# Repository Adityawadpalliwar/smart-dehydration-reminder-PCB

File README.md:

# Smart Hydration Reminder PCB

A compact, low-power, wireless-capable PCB designed to live in a water bottle base or sleeve. It detects when you drink using a 6-axis IMU, keeps a running record of intake events, and reminds you with a buzzer when you have gone too long without drinking. A companion phone app can connect over Bluetooth LE to adjust reminder intervals, mute alerts, read battery status and push firmware updates.

| | |
|---|---|
| **MCU** | Espressif ESP32-C3-MINI-1U-H4 (RISC-V, Wi-Fi + Bluetooth 5 LE) |
| **Motion sensing** | Bosch BMI270 6-axis IMU with wake-on-motion |
| **Power** | USB-C charging, 1S Li-ion/LiPo cell, 3.3 V LDO with hard-off slide switch |
| **Feedback** | Active buzzer, red/green battery LEDs, charge-status LED |
| **Input** | Tactile snooze/log button, slide power switch |
| **Board** | 4-layer PCB, 37.48 mm × 29.99 mm |

---

## Table of Contents

1. [Design Overview](#1-design-overview)
2. [System Architecture](#2-system-architecture)
3. [Power Subsystem](#3-power-subsystem)
4. [Compute and Connectivity](#4-compute-and-connectivity)
5. [Motion Sensing and Drinking Detection](#5-motion-sensing-and-drinking-detection)
6. [User Interface and Feedback](#6-user-interface-and-feedback)
7. [PCB Design](#7-pcb-design)
8. [Pin Assignment](#8-pin-assignment)
9. [Bill of Materials (Key Components)](#9-bill-of-materials-key-components)
10. [Power Considerations](#10-power-considerations)
11. [Known Limitations and Planned Improvements](#11-known-limitations-and-planned-improvements)
12. [Conclusion](#12-conclusion)

---

## 1. Design Overview

The platform combines motion intelligence, multi-modal alerts, low-power telemetry and dual-mode connectivity (Wi-Fi / Bluetooth LE) to monitor drinking patterns, track the interval between sips and deliver adaptive reminders.

The hardware is organised as four layers, each building on the one before:

| Layer | Function | Key parts |
|---|---|---|
| **Charging** | Safe single-cell Li-ion charging from USB-C | J1, USBLC6-2SC6, MCP73831 |
| **Power gating** | User-operated hard-off that shuts down the entire downstream system | S1, RT9080 LDO |
| **Compute and sense** | Application logic, radio, motion detection, battery monitoring | ESP32-C3-MINI-1U, BMI270 |
| **Feedback** | Audible reminders and visual status | Buzzer, LEDs, tactile button |

A central design decision is that the slide switch gates the **LDO itself**, not just the buzzer. Flipping it to OFF removes power from every downstream block (MCU, IMU, LEDs, buzzer driver), giving true zero downstream draw for storage or travel, while the charger and cell remain upstream so the battery still charges over USB regardless of switch position.

---

## 2. System Architecture

```mermaid
flowchart LR
    USB["USB-C receptacle (J1)"] --> ESD["ESD protection (U6)"]
    ESD -- "D+ / D-" --> MCU
    USB -- "VBUS" --> CHG["MCP73831 charger (U4)"]
    CHG --> BAT[("1S Li-ion / LiPo cell")]
    BAT --> LDO["RT9080 3.3 V LDO (IC1)"]
    SW["Slide switch (S1)"] -- "EN control" --> LDO
    LDO --> RAIL["3.3 V rail"]
    RAIL --> MCU["ESP32-C3-MINI-1U (U2)"]
    RAIL --> IMU["BMI270 IMU (U3)"]
    IMU -- "I2C + INT1" --> MCU
    BAT -- "Divider R14/R15" --> MCU
    MCU --> LEDS["Battery LEDs (D2, D3)"]
    MCU --> BUZ["Buzzer driver (Q1, U5)"]
    BTN["Push button (S2)"] --> MCU
```

Power flows from USB-C through the charger into the cell, then through the LDO to the 3.3 V rail. Data flows between the IMU, buttons and MCU, and the MCU drives the LEDs and buzzer.

---

## 3. Power Subsystem

### 3.1 USB-C Input and ESD Protection

- **Connector:** USB Type-C 16-pin receptacle (J1), used for USB 2.0 data (D+/D−) and VBUS/GND.
- **CC termination:** 5.1 kΩ pull-down resistors (R1, R2) on CC1 and CC2 identify the board as a sink, so a Type-C source enables VBUS at 5 V.
- **Transient protection:** A TVS diode array (U6, USBLC6-2SC6) sits directly beside the receptacle and clamps ESD on the data lines, rated to ±15 kV air discharge (IEC 61000-4-2).

### 3.2 Battery Charging

- **Charge controller:** Microchip MCP73831T-2ACI/OT (U4), SOT-23-5, constant-current / constant-voltage charging to 4.2 V.
- **Charge current:** Set by R5 on the PROG pin:

  ```
  I_CHG = 1000 V / R_PROG
  ```

  With R5 = 2 kΩ the fast-charge current is **500 mA**.
- **Status indication:** The open-drain STAT pin drives the charge LED (D1) through R4 = 4.7 kΩ. D1 is lit during the CC/CV phase and goes off (high-impedance) once charge terminates.
- **Cell:** 1S Li-ion/LiPo connected at pads J2/J3 (4.2 V max). A cell with a built-in protection circuit is required, as the board does not include its own over-discharge protection.

### 3.3 Hard-Off Power Switch

- **Switch:** C&K JS202011SCQN (S1), a subminiature surface-mount SPDT slide switch.
- **Rationale:** Rather than routing the ESP32-C3's high RF supply current (transmit spikes around 350 mA) through small mechanical switch contacts, which causes contact wear and voltage droop, the switch drives the high-impedance **EN** input of the LDO.
- **Wiring:**

  | S1 pin | Connection |
  |---|---|
  | Pin 1 (outer) | VBAT |
  | Pin 2 (common) | EN pin of IC1 |
  | Pin 3 (outer) | GND |

  R13 = 100 kΩ additionally ties EN to GND.
- **OFF state:** EN is driven to GND, the LDO enters shutdown (typically below 0.1 µA), and nothing downstream draws current.
- **Charging is independent of the switch.** The charger and cell sit upstream of the switch, so a switched-off device still charges.
- **Trade-off:** When switched off, the MCU cannot log the event, cannot save state beyond what is already in flash, and cannot be reached over BLE. This is intentional for a hard off.
- **Control roles:** The tactile button (S2) is the fast, momentary snooze/silence control. The slide switch is purely the full power gate.

### 3.4 3.3 V Regulation

- **Regulator:** Richtek RT9080-33GJ5 (IC1), TSOT-23-5.
- **Quiescent current:** about 2 µA typical, versus roughly 5 mA for a classic AMS1117-class regulator, which would drain a small cell in days.
- **Output capability:** 600 mA continuous, above the ESP32-C3 peak transient demand (about 500 mA system requirement).
- **Dropout:** 310 mV at 600 mA. Dropout scales with load, so at the light average loads of this application the regulator holds 3.3 V until the cell is nearly empty (about 3.0 V). Under a full 600 mA load, regulation needs roughly 3.6 V at the input. Use the ESP32-C3 brown-out detector for the low-voltage end.

---

## 4. Compute and Connectivity

### 4.1 MCU

- **Module:** Espressif ESP32-C3-MINI-1U-H4 (U2)
- **Core:** 32-bit single-core RISC-V, up to 160 MHz, 4 MB embedded flash
- **RF:** U.FL connector for an external antenna, which avoids the detuning that liquid volumes inside a water bottle would cause on an on-board antenna

The MCU runs the whole system: timers, the buzzer state machine, IMU handling, ADC readings, intake logging and the BLE/Wi-Fi link. Choosing a radio-capable MCU means app connectivity costs no additional hardware.

### 4.2 Mobile Ecosystem and Firmware Interoperability

- **BLE control:** A Bluetooth 5 LE GATT server lets the companion app modify reminder intervals, mute acoustic alerts, read real-time battery status and push over-the-air (OTA) firmware updates.
- **Intake logging:** Drinking events are stored locally in non-volatile storage (NVS flash) and batch-synchronised to the cloud when Wi-Fi is reachable.
- **Radio versus battery life:** BLE activity draws tens of milliamps while active, against microamps in deep sleep. The connection and advertising schedule directly trades app responsiveness (for example, muting a reminder remotely) against battery life, and is a key firmware tuning parameter.

---

## 5. Motion Sensing and Drinking Detection

### 5.1 Sensor

- **IC:** Bosch BMI270 (U3), a 16-bit ultra-low-power 6-axis IMU (3-axis accelerometer + 3-axis gyroscope).
- **Power:** below 685 µA in full-performance mode, and a few microamps in suspend.
- **Interface:** I²C on IO2 (SDA) and IO3 (SCL) with 4.7 kΩ pull-ups (R7, R8). Decoupling on C6/C7. Ensure CSB is strapped high for I²C mode and SDO is strapped to set the address.

### 5.2 Drinking Detection Algorithm

Motion processing runs directly in firmware:

1. **Pickup detection.** High-pass-filtered Z-axis acceleration thresholds detect the bottle being lifted from a resting surface.
2. **Tilt estimation.** Pitch and roll dynamics give the tilt angle relative to gravity:

   ```
   θ_tilt = atan2( A_y , sqrt(A_x² + A_z²) )
   ```
3. **Sip validation.** A sip event is confirmed when the tilt exceeds **45°** for at least **1.5 s**, followed by a controlled lowering movement.
4. **Timer reset.** Each verified sip resets the reminder countdown, so users who hydrate naturally are never nagged.

### 5.3 Deep Sleep with Wake-on-Motion

- BMI270 **INT1** (pin 4) connects to the RTC-capable pin **IO4** of the ESP32-C3.
- When idle, the ESP32-C3 sits in deep sleep (about 5 µA) while the BMI270 stays in its low-power motion-detect mode.
- Moving the bottle makes the BMI270 pulse INT1, waking the MCU to update intake telemetry and timer logs.

---

## 6. User Interface and Feedback

### 6.1 Battery Voltage Monitoring

- **Divider:** R14 = R15 = 100 kΩ halve the battery voltage:

  ```
  V_ADC = V_BAT × R15 / (R14 + R15) = V_BAT / 2
  ```
- **Range:** At V_BAT = 4.2 V, V_ADC = 2.1 V, inside the ESP32-C3 ADC range at 11 dB attenuation (0 to about 2.5 V). The divider feeds ADC pin **IO0**.
- **Noise filter:** C10 = 0.1 µF across R15 forms a low-pass filter with the 50 kΩ Thévenin resistance:

  ```
  f_c = 1 / (2π × 50 kΩ × 0.1 µF) ≈ 31.8 Hz
  ```

  This suppresses ripple from Wi-Fi/Bluetooth transmit bursts.
- **Firmware note:** The ESP32-C3 ADC is non-linear at the ends of its range, so use the calibrated ADC API (eFuse calibration values) rather than a simple linear conversion.

### 6.2 Visual Battery Telemetry

| LED | Colour | Pin | Resistor | Lit when |
|---|---|---|---|---|
| D3 | Green | IO5 | 470 Ω (R11) | V_BAT ≥ 3.5 V |
| D2 | Red | IO6 | 470 Ω (R12) | V_BAT < 3.5 V |
| D1 | Charge status | MCP73831 STAT | 4.7 kΩ (R4) | While charging |

Firmware drives IO5 high and IO6 low above the threshold, and the reverse below it.

### 6.3 Acoustic Alert Subsystem

- **Transducer:** TMB12A03 (U5), 3 V active electromagnetic buzzer.
- **Driver:** Alpha & Omega AO3400 N-channel MOSFET (Q1, SOT-23-3, V_DS = 30 V, I_D = 5.8 A) low-side switches the buzzer.
- **Gate drive:** IO7 (BUZZ net). R6 = 10 kΩ pulls the gate to GND so the buzzer cannot turn on during MCU reset or boot.
- **Flyback protection:** A 1N4148 diode (CR1) across the buzzer terminals clamps inductive spikes at turn-off.
- **Patterns:** The MCU gates IO7 using LEDC PWM to create beep rhythms, such as a gentle single chime versus an escalating pattern after ignored reminders. The same driver circuit serves every pattern.

### 6.4 Snooze and Log Button

- **Switch:** C&K PTS526 (S2), low-profile tactile.
- **Circuit:** IO1 with a 10 kΩ pull-up (R10) to 3.3 V and a 0.1 µF debounce capacitor (C9) to GND.
- **Short press (< 1 s):** acknowledges and silences an active alarm, and resets the reminder timer.
- **Long press (> 3 s):** manual logging trigger, or initiates Bluetooth pairing.

---

## 7. PCB Design

The board is a **four-layer PCB measuring 37.48 mm × 29.99 mm**, laid out to be as compact as possible so it fits inside a bottle base or sleeve.

### 7.1 Layer Stack-Up

| Layer | Role |
|---|---|
| **L1 (Top)** | Power distribution and component placement |
| **L2** | Continuous ground plane |
| **L3** | Signal routing |
| **L4 (Bottom)** | Power/ground pours and remaining routing |

The dedicated ground plane on L2 gives every top-layer signal a solid return path and keeps the RF-adjacent ESP32-C3 section and the mixed analogue/digital sections (ADC divider, I²C sensor) well referenced. Keeping signals on L3 between planes reduces coupling and improves noise immunity, and the power/ground pours on L4 keep supply impedance low across the board.

### 7.2 Placement

- **USB-C (J1)** on the left board edge for easy cable access, with the ESD array and CC resistors immediately beside it.
- **ESP32-C3 module (U2)** at the top centre, close to the board edge to keep the radio section clear of other circuitry.
- **BMI270 (U3)** and its pull-ups and decoupling near the MCU, keeping the I²C and interrupt traces short.
- **Charger (U4), LDO (IC1) and passives** grouped in the lower centre, keeping the power path compact.
- **Slide switch (S1) and tactile button (S2)** on the right edge for user access.
- **Buzzer (U5) and driver (Q1)** at the top right.
- **Battery pads (J2/J3)** on the left side beside the charging circuitry.

---

## 8. Pin Assignment

| MCU pin | Signal | Direction | Notes |
|---|---|---|---|
| IO0 | Battery voltage sense | Input (ADC) | Via R14/R15 divider, filtered by C10 |
| IO1 | Snooze/log button (S2) | Input | 10 kΩ pull-up, 0.1 µF debounce |
| IO2 | I²C SDA | Bidirectional | 4.7 kΩ pull-up (R7) |
| IO3 | I²C SCL | Output | 4.7 kΩ pull-up (R8) |
| IO4 | BMI270 INT1 | Input (RTC) | Deep-sleep wake source |
| IO5 | Green LED (D3) | Output | 470 Ω series resistor |
| IO6 | Red LED (D2) | Output | 470 Ω series resistor |
| IO7 | Buzzer drive (BUZZ) | Output (PWM) | Gate of Q1, 10 kΩ pull-down |

---

## 9. Bill of Materials (Key Components)

| Ref | Part | Function |
|---|---|---|
| J1 | USB Type-C 16-pin receptacle | Power and data input |
| U6 | USBLC6-2SC6 | ESD/TVS protection on USB data lines |
| U4 | MCP73831T-2ACI/OT | Single-cell Li-ion charger |
| IC1 | RT9080-33GJ5 | 3.3 V ultra-low-Iq LDO |
| S1 | C&K JS202011SCQN | Slide switch, hard-off (LDO enable) |
| U2 | ESP32-C3-MINI-1U-H4 | MCU with Wi-Fi/BLE, U.FL antenna |
| U3 | Bosch BMI270 | 6-axis IMU |
| Q1 | AO3400 | Logic-level N-MOSFET, buzzer low-side switch |
| U5 | TMB12A03 | 3 V active electromagnetic buzzer |
| CR1 | 1N4148 | Buzzer flyback diode |
| S2 | C&K PTS526 | Tactile snooze/log button |
| D1 / D2 / D3 | LEDs | Charge status / low battery (red) / battery OK (green) |
| J2 / J3 | Battery pads | 1S Li-ion/LiPo connection |
| R1, R2 | 5.1 kΩ | USB-C CC pull-downs |
| R4 | 4.7 kΩ | Charge LED resistor |
| R5 | 2 kΩ | Charge current programming |
| R6 | 10 kΩ | Buzzer gate pull-down |
| R7, R8 | 4.7 kΩ | I²C pull-ups |
| R10 | 10 kΩ | Button pull-up |
| R11, R12 | 470 Ω | LED series resistors |
| R13 | 100 kΩ | LDO EN pull-down |
| R14, R15 | 100 kΩ | Battery voltage divider |
| C9, C10 | 0.1 µF | Button debounce, ADC filter |

---

## 10. Power Considerations

Standby battery life is set by the sum of always-connected loads plus the deep-sleep floor of the MCU and IMU. From the values used in this design:

| Contributor | Approx. current | Basis |
|---|---|---|
| RT9080 quiescent | 2 µA | Datasheet typical |
| ESP32-C3 deep sleep | 5 µA | Datasheet typical |
| BMI270 motion-detect mode | Measure on hardware | Accelerometer must stay active |
| EN pull-down R13 (switch ON) | ≈ 42 µA | 4.2 V / 100 kΩ |
| Battery divider R14 + R15 | ≈ 21 µA | 4.2 V / 200 kΩ |

Radio activity dominates when active, so BLE connection intervals and advertising schedule should be chosen with a measured energy budget in mind.

---

## 11. Known Limitations and Planned Improvements

- **Always-on resistive loads.** R13 and the R14/R15 divider account for most of the standby current. Moving to values of about 1 MΩ or higher, or gating the divider from a GPIO, would substantially extend standby life.
- **Charge current.** 500 mA on a 450 mAh cell is roughly a 1.1C rate. Reducing it to about 250 mA (R5 ≈ 4 kΩ) is gentler on the cell and limits heat in the linear charger.
- **Buzzer control.** The active buzzer has a fixed internal tone, so PWM gives rhythm control rather than true volume or pitch control. A passive buzzer would enable both.
- **Battery indication.** A single 3.5 V threshold does not map linearly to state of charge. A lookup-table mapping and a blinking red LED for "critical" would improve the indication with no hardware change.
- **Cell protection.** The design assumes a protected cell. On-board over-discharge protection is a candidate for a future revision.

---

## 12. Conclusion

The Smart Hydration Reminder PCB packs a complete wireless, motion-aware product into a 37.48 mm × 29.99 mm four-layer board. The charging path, LDO-gated hard-off switch and low-quiescent-current regulator form a power architecture built around a small battery, where a switched-off device draws essentially nothing and still charges. The ESP32-C3 and BMI270 combination delivers sip detection, wake-on-motion, local logging and app connectivity on a single radio-capable MCU, while the buzzer and LED feedback keep the user interface simple and robust.

The four-layer stack-up with a dedicated ground plane keeps the compact layout electrically quiet, and the documented limitations give a clear path to a longer-lasting, more refined next revision.

---

<p align="center"><sub>Smart Hydration Reminder · 4-layer hardware platform · 37.48 × 29.99 mm</sub></p>

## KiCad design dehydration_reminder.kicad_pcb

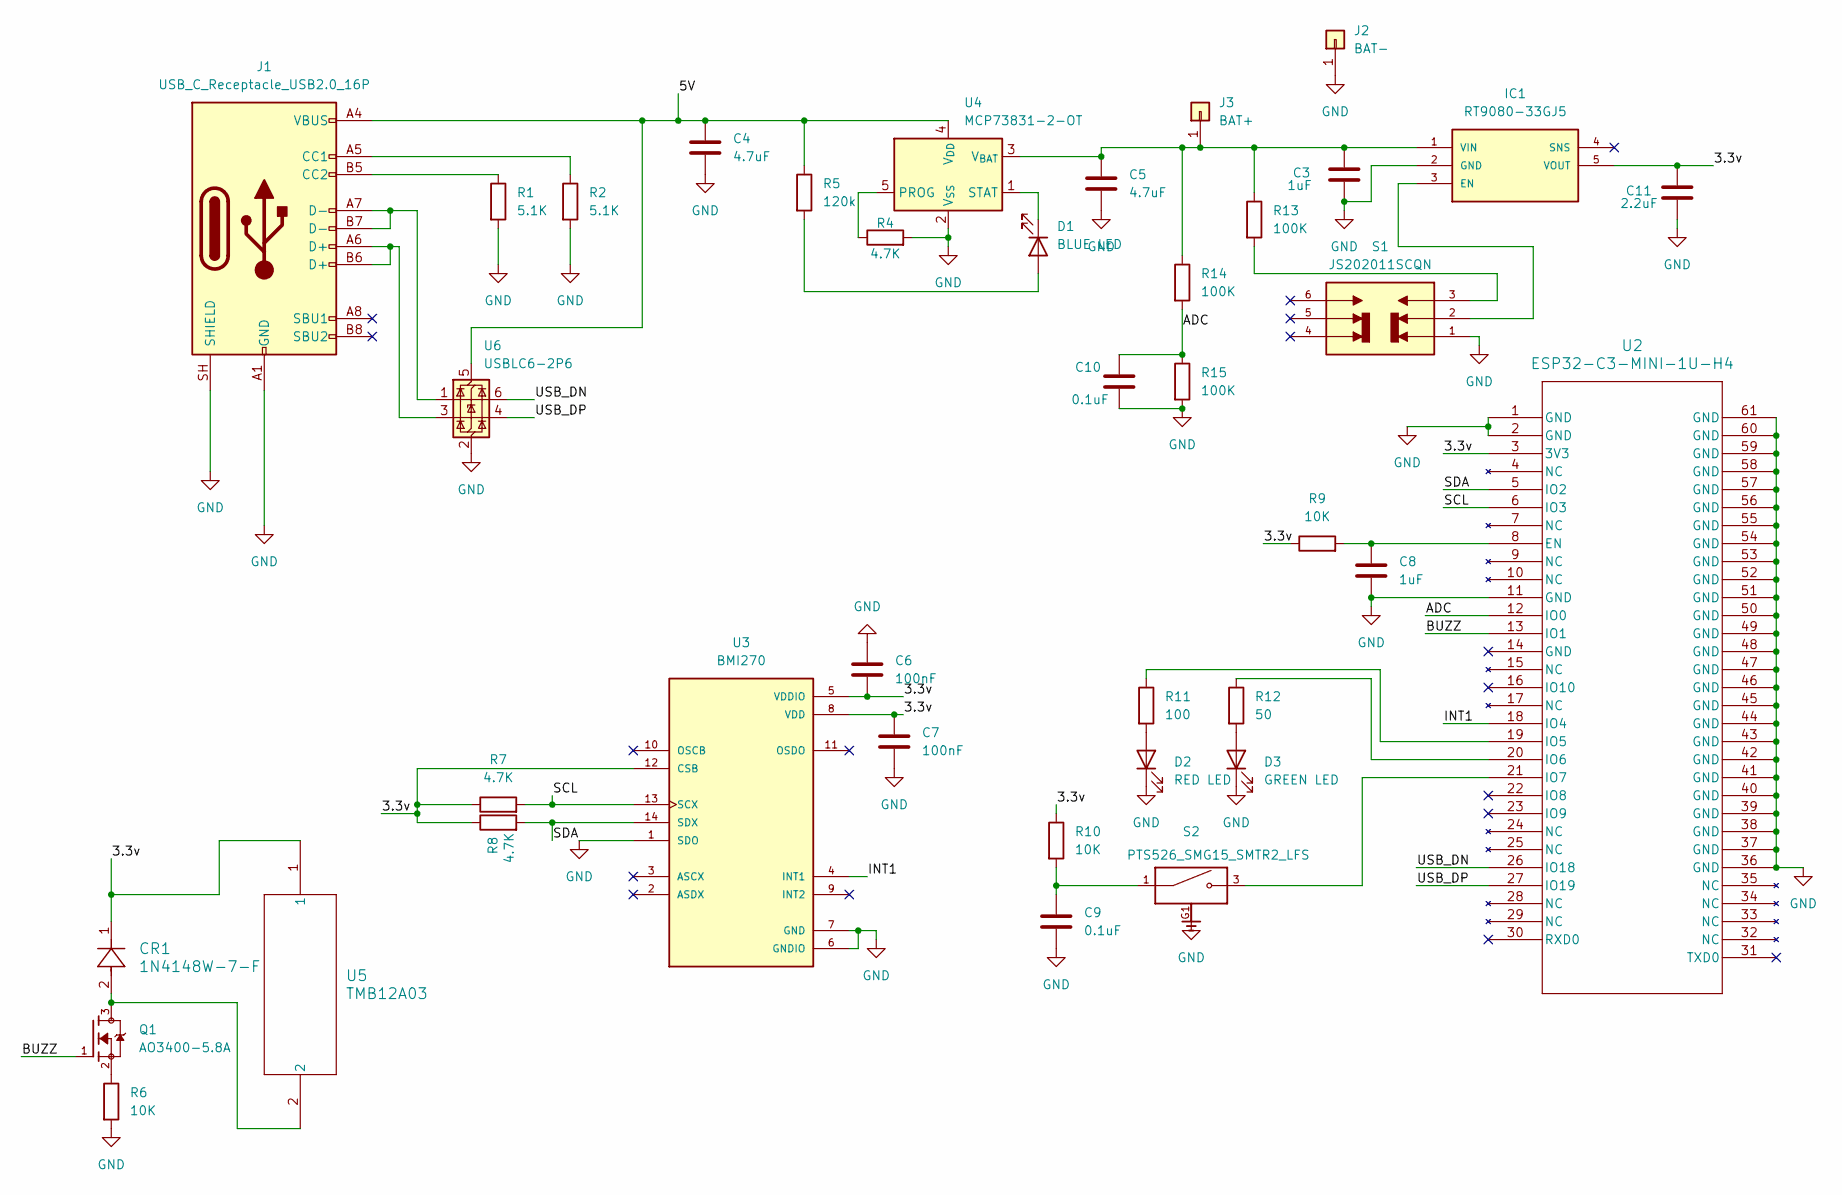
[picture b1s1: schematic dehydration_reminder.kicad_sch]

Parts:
C3, C8: 1uF; C_0805_2012Metric
C4, C5: 4.7uF; C_0805_2012Metric
C6, C7: 100nF; C_0603_1608Metric
C9, C10: 0.1uF; C_0603_1608Metric
C11: 2.2uF; C_0805_2012Metric
CR1: 1N4148W-7-F; SOD123_DIO
D1: BLUE LED; LED_0402_1005Metric_Pad0.77x0.64mm_HandSolder
D2: RED LED; LED_0402_1005Metric_Pad0.77x0.64mm_HandSolder
D3: GREEN LED; LED_0402_1005Metric_Pad0.77x0.64mm_HandSolder
IC1: RT9080-33GJ5; SOT94P280X100-5N
J1: USB_C_Receptacle_USB2.0_16P; USB_C_Receptacle_HRO_TYPE-C-31-M-12
J2: BAT-; SolderWirePad_1x01_SMD_1x2mm
J3: BAT+; SolderWirePad_1x01_SMD_1x2mm
Q1: AO3400-5.8A; SOT95P260X140-3N; PARTREV A2
R1, R2: 5.1K; R_0603_1608Metric
R4, R7, R8: 4.7K; R_0603_1608Metric
R5: 120k; R_0603_1608Metric
R6, R9, R10: 10K; R_0603_1608Metric
R11: 100; R_0603_1608Metric
R12: 50; R_0603_1608Metric
R13, R14, R15: 100K; R_0603_1608Metric
S1: JS202011SCQN; SW_JS202011SCQN; PARTREV 26 May 22
S2: PTS526_SMG15_SMTR2_LFS; SW_PTS526_SMG15_SMTR2_LFS; PARTREV 20 Nov 20; DigiKey_Part_Number CKN12222-1-ND
U2: ESP32-C3-MINI-1U-H4; ESP32-C3-MINI-1U_EXP
U3: BMI270; XDCR_BMI270
U4: MCP73831-2-OT; SOT-23-5
U5: TMB12A03; AUDIO_TMB12A03_JHE
U6: USBLC6-2P6; SOT-666

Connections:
/3.3v: C6.2, C7.1, C11.1, CR1.1, IC1.5 (VOUT), R7.1, R8.1, R9.1, R10.1, U2.3 (3V3), U3.5 (VDDIO), U3.8 (VDD), U3.12 (CSB), U5.1
/5V: C4.1, J1.A4 (VBUS), J1.A9 (VBUS), J1.B4 (VBUS), J1.B9 (VBUS), R5.1, U4.4 (V_{DD}), U6.5 (VBUS)
/ADC: C10.1, R14.2, R15.1, U2.12 (IO0)
/BUZZ: Q1.1, U2.13 (IO1)
/INT1: U2.18 (IO4), U3.4 (INT1)
/SCL: R7.2, U2.6 (IO3), U3.13 (SCX)
/SDA: R8.2, U2.5 (IO2), U3.14 (SDX)
/USB_DN: U2.26 (IO18), U6.6 (I/O1)
/USB_DP: U2.27 (IO19), U6.4 (I/O2)
GND: C3.2, C4.2, C5.2, C6.1, C7.2, C8.2, C9.2, C10.2, C11.2, D2.1 (K), D3.1 (K), IC1.2 (GND), J1.A1 (GND), J1.A12 (GND), J1.B1 (GND), J1.B12 (GND), J1.SH (SHIELD), J2.1 (Pin_1_1), R1.2, R2.2, R4.2, R6.2, R15.2, S1.1, S2.G1, S2.G2, U2.1 (GND), U2.2 (GND), U2.11 (GND), U2.36 (GND), U2.37 (GND), U2.38 (GND), U2.39 (GND), U2.40 (GND), U2.41 (GND), U2.42 (GND), U2.43 (GND), U2.44 (GND), U2.45 (GND), U2.46 (GND), U2.47 (GND), U2.48 (GND), U2.49 (GND), U2.50 (GND), U2.51 (GND), U2.52 (GND), U2.53 (GND), U2.54 (GND), U2.55 (GND), U2.56 (GND), U2.57 (GND), U2.58 (GND), U2.59 (GND), U2.60 (GND), U2.61 (GND), U3.1 (SDO), U3.6 (GNDIO), U3.7 (GND), U4.2 (V_{SS}), U6.2 (GND)
unnamed: C9.1, R10.2, S2.1, S2.2
unnamed: CR1.2, Q1.3, U5.2
unnamed: D1.2 (A), R5.2
unnamed: D1.1 (K), U4.1 (STAT)
unnamed: D2.2 (A), R11.2
unnamed: D3.2 (A), R12.2
unnamed: IC1.3 (EN), S1.2
unnamed: C3.1, C5.1, IC1.1 (VIN), J3.1 (Pin_1_1), R13.1, R14.1, U4.3 (V_{BAT})
unnamed: J1.A5 (CC1), R2.1
unnamed: J1.B5 (CC2), R1.1
unnamed: J1.A6 (D+), J1.B6 (D+), U6.3 (I/O2)
unnamed: J1.A7 (D-), J1.B7 (D-), U6.1 (I/O1)
unnamed: Q1.2, R6.1
unnamed: R13.2, S1.3
unnamed: C8.1, R9.2, U2.8 (EN)
unnamed: R11.1, U2.19 (IO5)
unnamed: R12.1, U2.20 (IO6)
unnamed: S2.3, S2.4, U2.21 (IO7)
unnamed: R4.1, U4.5 (PROG)

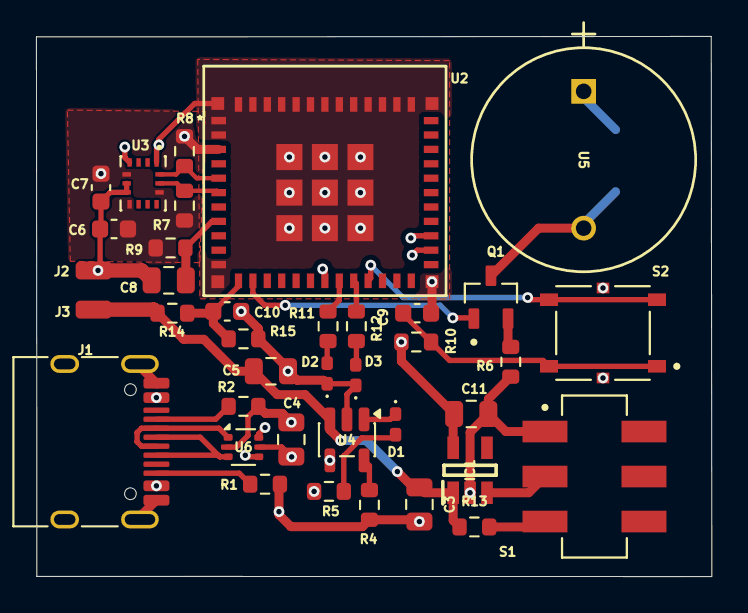
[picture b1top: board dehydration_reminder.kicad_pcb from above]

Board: 4 copper layers, 37.5 x 30.0 mm, 39 parts (1 on the bottom side), 29 nets.

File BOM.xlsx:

Reference | Qty | Value | Footprint | Price | Purchase-URL
C1 | 1.0 | 4.7nF | Capacitor_SMD:C_0603_1608Metric | 3.59 | https://robu.in/product/gcm188r91h472ka37d-murata-electronic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
C3,C8 | 2.0 | 1uF | Capacitor_SMD:C_0805_2012Metric | 4.97 | https://robu.in/product/cc0805kkx7r0bb105-yageo-100v-1uf-x7r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
C4,C5 | 2.0 | 4.7uF | Capacitor_SMD:C_0805_2012Metric | 1.89 | https://robu.in/product/0805x475k500nt-fh-50v-4-7uf-x5r%c2%b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
C6,C7 | 2.0 | 100nF | Capacitor_SMD:C_0603_1608Metric | 4.2 | https://robu.in/product/cc0603jrx7r7bb104-yageo-16v-100nf-x7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
C9,C10 | 2.0 | 0.1uF | Capacitor_SMD:C_0603_1608Metric | 0.3 | https://robu.in/product/cc0603jrx7r7bb104-yageo-16v-100nf-x7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
C11 | 1.0 | 2.2uF | Capacitor_SMD:C_0805_2012Metric | 1.14 | https://robu.in/product/2-2-uf-10000nf-25-v-capacitor-0805-s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
CR1 | 1.0 | 1N4148W-7-F | footprints2:SOD123_DIO | 2.22 | https://robu.in/product/1n4148-surface-mount-zener-diode-pac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
D1 | 1.0 | BLUE LED | LED_SMD:LED_0402_1005Metric_Pad0.77x0.64mm_HandSolder | 1.52 | https://robu.in/product/0402-surface-mount-led-blue-50-pcs/
D2 | 1.0 | RED LED | LED_SMD:LED_0402_1005Metric_Pad0.77x0.64mm_HandSolder | 0.97 | https://robu.in/product/0402-surface-mount-led-red-50pcs/
D3 | 1.0 | GREEN LED | LED_SMD:LED_0402_1005Metric_Pad0.77x0.64mm_HandSolder | 1.91 | https://robu.in/product/0402-surface-mount-led-green-50-pcs/
IC1 | 1.0 | RT9080-33GJ5 | RT9080-33GJ5:SOT94P280X100-5N | 14.0 | https://robu.in/product/rt9080-33gj5-richtek-ldo-voltage-reg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
J1 | 1.0 | USB_C_Receptacle_USB2.0_16P | Connector_USB:USB_C_Receptacle_HRO_TYPE-C-31-M-12 | 30.0 | https://robu.in/product/type-c-31-m-17-hroparts-1-6p-female-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
J2 | 1.0 | BAT- | Connector_Wire:SolderWirePad_1x01_SMD_1x2mm
J3 | 1.0 | BAT+ | Connector_Wire:SolderWirePad_1x01_SMD_1x2mm
Q1 | 1.0 | AO3400-5.8A | AO3400-5.8A:SOT95P260X140-3N | 8.0 | https://robu.in/product/ao3400-xblw-30v-5-8a-34m%25cf%25894-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
R1,R2 | 2.0 | 5.1K | Resistor_SMD:R_0603_1608Metric | 0.2 | https://robu.in/product/rc0603jr-075k1l-yageo-res-thick-film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
R3 | 1.0 | 1M | Resistor_SMD:R_0603_1608Metric | 1.34 | https://robu.in/product/1m-ohm-1-4w-0603-surface-mount-chip-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
R4,R7,R8 | 3.0 | 4.7K | Resistor_SMD:R_0603_1608Metric | 0.35 | https://robu.in/product/4-7k-ohm-1-4w-0603-surface-mount-chi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
R5 | 1.0 | 120k | Resistor_SMD:R_0603_1608Metric | 2.31 | https://robu.in/product/rt0603brd07120kl-yageo-smd-chip-resi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
R6,R9,R10 | 3.0 | 10K | Resistor_SMD:R_0603_1608Metric | 0.86 | https://robu.in/product/10k-ohm-1-4w-0603-surface-mount-chip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
R11 | 1.0 | 100.0 | Resistor_SMD:R_0603_1608Metric | 0.86 | https://robu.in/product/100-ohm-1-4w-0603-surface-mount-chip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
R12 | 1.0 | 50.0 | Resistor_SMD:R_0603_1608Metric | 0.68 | https://robu.in/product/ac0402jr-0750rl-yageo-res-thick-film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
R13,R14,R15 | 3.0 | 100K | Resistor_SMD:R_0603_1608Metric | 0.45 | https://robu.in/product/100k-ohm-1-4w-0603-surface-mount-chi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
S1 | 1.0 | JS202011SCQN | JS202011SCQN:SW_JS202011SCQN | 37.0 | https://robu.in/product/js202011scqn-ck-300ma-standing-paste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
S2 | 1.0 | PTS526_SMG15_SMTR2_LFS | PTS526_SMG15_SMTR2_LFS:SW_PTS526_SMG15_SMTR2_LFS | 13.0 | https://robu.in/product/pts526-spg15-smtr2-lfs-ck-5-2mm-1-5m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
U2 | 1.0 | ESP32-C3-MINI-1U-H4 | footprints3:ESP32-C3-MINI-1U_EXP | 249.0 | https://robu.in/product/espressif-esp32-c3-mini-1-h4-module/
U3 | 1.0 | BMI270 | BMI270:XDCR_BMI270 | 569.0 | https://robu.in/product/bosch-bmi270motion-sensoric22-g-4-g-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
U4 | 1.0 | MCP73831-2-OT | Package_TO_SOT_SMD:SOT-23-5 | 139.0 | https://robu.in/product/mcp73831t-2aci-ot-4-2v-500ma-single-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
U5 | 1.0 | TMB12A03 | footprints4:AUDIO_TMB12A03_JHE | 22.0 | https://robu.in/product/tmb12a03-cldz-electromagnetic-active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
U6 | 1.0 | USBLC6-2P6 | Package_TO_SOT_SMD:SOT-666 | 14.0 | https://robu.in/product/usblc6-2sc6-stmicroelectronics-usblc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
BT1 | 1.0 | 450mAh LiPo battery | (not in schematic) | 299.0 | https://robu.in/product/450mah-pcm-protected-micro-li-po-battery/
Y1 | 1.0 | 32.768kHz crystal | (not in schematic) | 41.0 | https://robu.in/product/yxc-32-768-khz-12-5-pf-tuning-fork-q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
TOTAL |  |  |  | 1464.76
